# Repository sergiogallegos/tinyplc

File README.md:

# tinyplc

A research PLC built around **Structured Text → Rust frontend → LLVM IR →
ahead-of-time machine code → a C runtime on FreeRTOS/STM32**. LLVM runs on the
PC. The microcontroller schedules and executes already-compiled user logic.
The initial target is the NUCLEO-F446RE.

**Education and research only. Do not use tinyplc for real machines or safety
functions.** Output fault handling is not a certified safety system.

Repository: [sergiogallegos/tinyplc](https://github.com/sergiogallegos/tinyplc).

## Custom hardware prototype

The [hardware roadmap](docs/hardware-roadmap.md) describes a standalone tinyPLC.
The [A1 completion checklist](docs/tasks.md#a1-prototype-completion) tracks the
remaining BOM, electrical, mechanical, firmware and validation work.
The current [A1 prototype draft](hardware/prototype-a1/README.md) includes a
custom KiCad schematic and **routed two-layer PCB**, a rounded white FreeCAD
enclosure, physical power switch, OLED/status-indicator design, print files,
dimensioned drawings, BOM and official component references. Start with the
[product brochure](hardware/prototype-a1/brochure/tinyplc-a1-brochure.pdf) or the
[visual assembly guide](hardware/prototype-a1/mechanical/drawings/assembly-guide.pdf).
The PCB passes ERC and DRC with zero unrouted connections. Independent fabrication
review, physical testing, the standalone firmware port and OLED/heartbeat
integration remain outstanding. See the [routing decisions and checks](docs/hardware/prototype-a1-routing.md). The original
[A0 package](hardware/prototype-a/README.md) is preserved for comparison.

The enclosure is a Blender render; the board view comes from the routed KiCad
design. The display shows a proposed demo UI. [Rear connector view](hardware/prototype-a1/renders/rear-power.png).

## Current state: compile, download and activate native ST on STM32

Implemented: a dependency-free Rust ST frontend, positioned diagnostics,
separate typed PLC IR, textual LLVM IR emission, exported tag metadata, and a
C-compatible scan entry point. Tests verify IR, execute host machine code at
`-O0` and `-O2`, compare results with independent historical interpreters, and
cross-compile to ARM Cortex-M object code. A static FreeRTOS task now runs
linked ST machine code from RAM on the F446, samples PC13, commits PA5, latches
faults and measures the 10 ms release schedule. ST now executes in a separate
unprivileged task, with checked return, MPU isolation, TIM2 deadline abort and
IWDG reset fallback. R2 is complete; see the [consolidated report](docs/R2-report.md).

The [R3.1 wire contract](docs/wire-format.md) now defines native packages and
engineering frames, with generated Rust/C constants and golden fixtures.

[R3.2](docs/R3.2-report.md) adds the Rust native packager and portable C
package validation/staging, tested together on the host.

[R3.3](docs/R3.3-report.md) connects the board over USB serial: `plctool` downloads
into an inactive slot, explicitly activates a generation, and reports execution
status. Downloaded code runs unprivileged with validated tag bindings and a
fresh worker context. Both slots and 64-tag execution have hardware evidence.

[R3.4](docs/R3.4-report.md) adds owned snapshots and `plctool DEVICE monitor`,
with host concurrency tests and target build validation.
[R3.5](docs/R3.5-report.md) verifies the full board workflow and mixed download/monitor
traffic: a 4.054 ms maximum observed scan body within the 10 ms period, with no
missed releases in the recorded run. R3 is complete.

[R4](docs/R4.2-report.md) adds compatible VAR migration, a reserved first-scan
trial and one-use rollback to saved pre-update state. [Board evidence](docs/R4.3-report.md)
covers 64-tag reorder, contained faults, recovery failure and reset behavior.

[R5.1](docs/ton.md) adds native TON on-delay timers and millisecond TIME values,
with frozen clock input and explicit restart behavior for online changes. See
[the example](examples/ton_led.st) and [acceptance report](docs/R5.1-report.md).

**Not implemented yet:** tag writes, persistence or broader language types.

The primary compiler is `compiler/` (Rust). Earlier Python/bytecode work is
retained only as a historical semantic test reference; it is not the product
architecture or a planned fallback execution mode.

## Try it on the PC

Use existing Rust/Cargo, LLVM (`clang`, `llvm-as`, `opt`), Python 3.11+, CMake,
a C compiler, and ARM GNU ld for the package integration tests. No packages are fetched by these commands.

```sh
make compiler
./target/debug/plcc examples/button_led.st -o /tmp/button_led.ll
make run
make aot-arm
make test
```

`make run` compiles the example through Rust and LLVM, links it with a C host
harness, and prints `R1 AOT scans=5 LED=1 N=2`. `make aot-arm` creates
`build/aot/button_led.arm.o`, an ARM relocatable object. It does not upload,
link firmware, or flash a board. [Compiler usage and ABI](compiler/README.md)
and [setup](docs/setup.md) give exact reproduction commands.

## Compile, upload, and run on the board

The NUCLEO-F446RE must already have the current R5.1 runtime firmware installed
through ST-LINK. Firmware prerequisites and build instructions are in
[setup](docs/setup.md) and the [target toolchain guide](docs/target-toolchain.md).
The following workflow uploads an ST program through the ST-LINK virtual serial
port; it does not replace the runtime firmware.

After a board reset, the boot program occupies slot A and slot B is available.
Use your actual serial device path and installed toolchain paths:

```sh
make compiler
mkdir -p build/programs
PLC_DEVICE=/dev/cu.usbmodem2103
./target/debug/plctool "$PLC_DEVICE" info
./target/debug/plcpack examples/ton_led.st --slot B -o build/programs/ton-b.tplc \
  --clang /path/to/clang --ld /path/to/arm-none-eabi-ld
./target/debug/plctool "$PLC_DEVICE" download build/programs/ton-b.tplc
```

`plcpack` compiles ST, generates ARM code, links for the chosen slot, and builds
the download package. Download returns a JSON `ready_generation`; substitute
that number for `GENERATION` below:

```sh
./target/debug/plctool "$PLC_DEVICE" activate GENERATION
./target/debug/plctool "$PLC_DEVICE" status
./target/debug/plctool "$PLC_DEVICE" monitor
./target/debug/plctool "$PLC_DEVICE" update-status
```

Activation starts execution on the board's **10 ms scan cycle**. In this example,
hold BTN for 500 ms to light LED; releasing BTN clears the timer and LED on the
next invocation. `monitor` prints one coherent snapshot, including TON Q/ET
and the clock; run it again for another sample. TIME values are milliseconds.

For subsequent edits, inspect `info` and build for the inactive slot: A is
`0x20010000`, B is `0x20014000`, and ACTIVE has state 1. The download command
rejects a package built for the wrong available slot. Downloading only stages
code; `activate` is required to run it. See [package usage](packager/README.md)
and [engineering commands](engineering/README.md) for details.

Healthy online updates preserve matching scalar VAR names/types. TON instances
restart their delays. `plctool "$PLC_DEVICE" rollback` restores the saved previous
program and scalar state when a checkpoint is available; timers restart again.
Starting another download retires that checkpoint. Downloads and state are
RAM-only: reset or power loss returns to the firmware's boot program.

## How the system works

### 1. Compile on the PC; execute on the controller

```mermaid
flowchart TB
  subgraph PC["PC — frontend and AOT code generation implemented"]
    ST["ST source<br/>IEC 61131-3 subset"] --> Front["Rust frontend<br/>lexer, parser, semantic checks"]
    Front --> IR["Typed PLC IR<br/>tags, types, expressions, control flow"]
    IR --> LLVM["LLVM IR"]
    LLVM --> Object["LLVM ahead-of-time compiler<br/>ARM Cortex-M object code"]
    Object --> Experiment["Boot program<br/>static firmware link into slot A"]
    Experiment --> Runtime
    Object --> Link["Host link for slot A or B<br/>all addresses resolved on PC"]
    Link --> Package["Rust plcpack<br/>ABI, state layout, code, integrity metadata"]
  end
  Package -->|"plctool over ST-LINK USB serial"| Loader
  subgraph Board["STM32 — isolated native scan experiment implemented"]
    Loader["Low-priority C comms and loader<br/>validate, stage and seal inactive slot"]
    Loader --> Activate["Accept generation at scan boundary<br/>prepare state and protection context"]
    Activate --> Runtime["C supervisor on FreeRTOS<br/>periodically invokes native entry"]
    Runtime --> Worker["Unprivileged ST worker<br/>private stack and MPU permissions"]
    Worker --> Gate["Firmware-flash return gateway<br/>TIM2 deadline and watchdog fallback"]
    Gate --> Runtime
    Runtime --> IO["Input sampling and output commit"]
    Runtime --> Tags["Runtime-owned schema and values<br/>validated bindings, frozen I/O"]
    Tags --> Monitor["Coherent tag snapshots<br/>PC monitoring"]
  end
  classDef implemented fill:#e1f5ef,stroke:#39927d,color:#064f43;
  classDef planned fill:#f2f2f2,stroke:#888,color:#333;
  class ST,Front,IR,LLVM,Object,Link,Package,Experiment,Runtime,Worker,Gate,IO,Loader,Activate,Tags implemented;
  class Monitor implemented;
```

Green is implemented; the R3.4 report distinguishes host tests from board evidence. The C
runtime is firmware installed through ST-LINK. The user program is a separate
native artifact downloaded through the engineering connection. A general
Linux `.so` or an unqualified raw `.bin` is not our MCU loading contract.

### 2. Scan ownership and monitoring

**Full target design.** Scheduling, sampled inputs, working/committed state,
physical outputs, fault latching, unprivileged execution and native deadline
abort are implemented in the [scan supervisor](docs/scan-runtime.md) and
[execution boundary](docs/native-isolation.md). Owned tag snapshots are implemented in R3.4; tag-write boundary requests remain planned.

```mermaid
flowchart TB
  subgraph Scan["C scan supervisor — highest application priority"]
    Read["Sample physical inputs<br/>freeze input image"] --> Working["Prepare working state<br/>arm deadline guard"]
    Working --> Run["Invoke compiled native logic<br/>bounded unprivileged execution"]
    Run --> Check["Trusted return or abort<br/>commit success / discard failed work"]
    Check --> Outputs["Apply physical outputs<br/>FALSE on fault"]
    Outputs --> Publish["Publish coherent snapshot<br/>tags, scan ID, generation, diagnostics"]
    Publish --> Boundary["Apply accepted boundary request<br/>then wait for next release"]
    Boundary --> Read
  end
  subgraph Comms["Lower-priority engineering task"]
    Receive["Receive command"] --> Stage["Stage native image<br/>validate before READY"]
    Receive --> Request["Request activation/rollback<br/>bounded payload + generation"]
    Receive --> Monitor["Read owned snapshot<br/>respond to PC monitor"]
  end
  Request -. "scan owner applies" .-> Boundary
  Publish -. "three-buffer ownership mailbox" .-> Monitor
  Working -. "independent guard interrupts a stuck program" .-> Abort["Abort user context<br/>output policy + fault recovery"]
```

Comms never reads a tag by racing a live write or retaining a pointer into a
reusable program slot. A snapshot contains values **and** names/types/scan and
generation identifiers. A slow monitor may miss scans without blocking the
producer. Tag writes remain unimplemented; the planned design routes them through the scan owner.

Native code addresses fields relative to a supplied state block. The symbol
metadata maps names to types/classes and offsets; it does not embed arbitrary
addresses in privileged runtime memory. Inputs are frozen and outputs are
proposals until commit. The initial research ABI uses one u32 cell per tag,
with byte offset `4 × declaration index`.

### 3. Edit, download, accept, observe

**Implemented download/activation workflow.** Download success and activation
success are separate states; R3.4 adds coherent tag snapshots.

```mermaid
sequenceDiagram
  actor User as Engineer
  participant PC as Rust frontend + LLVM + engineering CLI
  participant Loader as C loader / comms
  participant Scan as FreeRTOS scan supervisor
  User->>PC: Edit ST and build target native image
  PC->>Loader: Transfer bounded chunks
  Loader->>Loader: Validate package, ABI, exact slot and state schema
  Loader-->>PC: READY with candidate generation
  Note over Loader,Scan: Current program keeps running
  User->>PC: Accept edit
  PC->>Loader: ACTIVATE(candidate generation)
  Loader-->>PC: Request accepted, not yet running
  Loader->>Scan: Publish owned boundary request
  Scan->>Scan: Migrate compatible VARs and install a fresh native worker
  Scan->>Scan: Execute first candidate scan under deadline guard
  alt Successful execution
    Scan-->>Loader: Snapshot confirms running generation
  else Contained application fault
    Scan->>Scan: Outputs FALSE, discard candidate working state
    Scan->>Scan: Restore healthy checkpoint at the next release, if available
    Scan-->>Loader: Fault and rejected generation retained
  end
  PC->>Loader: Read execution status
  Loader-->>PC: Actual generation, outcome, fault and timing
  PC-->>User: Confirm the edit outcome
```

R4 migration matches exact internal variable names and types. Explicit rollback
restores saved pre-update values and consumes its checkpoint.
Inputs are resampled and outputs recomputed. Preserved variables do not
promise unchanged output behavior; rollback cannot undo physical actions.
Two slots cannot preserve active, previous, and another candidate at once.
Slot reservations and generation checks are required; a pending flag and
pointer flip alone are insufficient.

## Structured Text scope

The initial language is a small **IEC 61131-3-inspired ST subset**, not full
IEC conformance: BOOL, DINT, TIME, input/output/internal declarations,
assignments, IF/ELSIF/ELSE, DINT arithmetic, comparisons, eager boolean logic,
comments, and TON on-delay timers with IN/PT inputs and Q/ET outputs.
TIME supports nonnegative millisecond durations and comparisons, not arithmetic.
See [language.md](docs/language.md) and [TON](docs/ton.md) for exact grammar,
clock behavior, and limits: 64 expanded cells, including five per timer and one
shared clock cell. General function blocks and loops are not supported.

```iecst
PROGRAM Main
VAR_INPUT BTN : BOOL; END_VAR
VAR_OUTPUT LED : BOOL; END_VAR
VAR n : DINT; END_VAR
IF BTN THEN n := n + 1; END_IF;
LED := NOT BTN;
END_PROGRAM
```

`N` increments on every scan with BTN pressed, not once per press. DINT wraps
modulo 2^32. Division by zero reports a fault; minimum DINT divided by -1 wraps.
The Rust emitter preserves these rules explicitly instead of relying on LLVM
undefined behavior. [LLVM division semantics](https://llvm.org/docs/LangRef.html#sdiv-instruction).

## Hardware

The NUCLEO-F446RE contains an STM32F446RE Cortex-M4F, an onboard ST-LINK/V2-1 debugger, a user LED, and a user button. Connect a USB **data** cable to ST-LINK CN1. No external I/O circuitry is needed for the first example. This board provides 3.3 V logic; industrial 24 V inputs and outputs would need separate conditioning and protection hardware.

| Resource | Project mapping | Verification and qualification |
| --- | --- | --- |
| LD2 green user LED | `LED` → PA5, HIGH lights it | UM1724 §7.6 and Table 19 |
| B1 user button | `BTN` → PC13, inverted for pressed = TRUE | UM1724 §7.7 confirms pin; polarity must match board schematic/revision before hardware acceptance |
| ST-LINK virtual COM port | USART2: PA2 TX, PA3 RX | UM1724 §7.10, default solder bridges SB13/SB14 connected |
| Serial configuration | 115200 baud, 8 data bits, no parity, 1 stop bit | Chosen firmware setting, not a fixed hardware setting |
| Memory | 512 KB flash, 128 KB main SRAM | STM32F446xC/E datasheet; also 4 KB backup SRAM, unused in v1 |
| Ethernet | No onboard Ethernet interface | Use UART on the board; host TCP transport is planned |

On macOS a VCP commonly appears as `/dev/tty.usbmodem*` and `/dev/cu.usbmodem*`; discover the actual path rather than hardcoding it. A detected device does not prove the firmware works. The hardware references are [ST UM1724 Rev 17](https://www.st.com/resource/en/user_manual/dm00105823.pdf), [STM32F446 datasheet](https://www.st.com/resource/en/datasheet/stm32f446re.pdf), and [MB1136 C04 schematic, MCU sheet](https://www.st.com.cn/resource/en/schematic_pack/mb1136-default-c04_schematic.pdf). The requested facts are consistent with these qualifications: baud and Mac device path are configuration/environment choices, and 128 KB excludes backup SRAM.

The Rust CLI currently uses built-in logical bindings for `BTN` (BOOL input)
and `LED` (BOOL output). The [board profile](boards/nucleo_f446re.json) records
the physical mapping; the C board port applies it. The compiler library
also accepts an explicit list of logical bindings. No register access is emitted
into user logic.

See the [educational design and compiler/runtime studies](docs/education.md) for the reading
order, dependency boundary, and reasons for using a small STM32 board.

## Repository responsibilities

| Directory | Role |
| --- | --- |
| `compiler/` | Primary Rust lexer/parser, semantic analysis, typed PLC IR, LLVM emitter, CLI, scan ABI, tests |
| `contract/` | Shared wire definitions and generated Rust/C constants |
| `packager/`, `engineering/` | Rust native package builder and serial engineering CLI |
| `runtime/` | Portable C scan transaction, package validator, staging and framing |
| `sim/aot_main.c` | Current C harness invoking host AOT machine code |
| `port/` | STM32 C/FreeRTOS supervisor, GPIO/UART, MPU, deadline and fault handling; historical blink |
| `tests/llvm/` | IR verification, optimized host AOT execution, ARM codegen and semantic comparisons |
| `boards/` | Explicit target I/O mapping; native profiles are documented in `docs/` |
| `core/`, `host/`, `tests/native/` | Historical M1/M2 implementation and independent test oracles |
| `docs/` | Current architecture, compiler contract, native loader roadmap, reports and historical designs |

The Rust frontend uses only its standard library. LLVM is a PC-side toolchain
dependency; no LLVM library or compiler runs on the MCU. FreeRTOS is the
scheduler dependency. The project owns PLC semantics, the native image/ABI
contract, engineering operations, and runtime state management.

## Roadmap after the architecture change

| Stage | Deliverable | Status |
| --- | --- | --- |
| M0–M2 | Initial board scaffold, C VM, Python compiler and independent execution tests | Historical; retained for evidence and test reuse |
| R1 | Rust ST frontend → typed PLC IR → LLVM IR; host AOT and Cortex-M object generation | Implemented and host-tested |
| R2 | Native ABI/package contract, C supervisor, bounded static native execution and fault containment on F446 | Complete, including hardware evidence |
| R3 | Native loader, upload protocol, engineering CLI and coherent tag monitoring | Complete, including board monitoring and mixed-traffic timing |
| R4 | Online state migration, first-scan trial and explicit/automatic rollback | Implemented and verified on the board |
| R5.1 | TON on-delay timers, TIME, frozen clock input and restart-on-update behavior | Complete, including host and board acceptance |
| Further R5 work | Additional language features, source debugging, persistence and target ports | Future extensions |

R1 replaces the earlier bytecode-first roadmap. No MCU loading, RTOS timing,
or hardware acceptance is implied by host tests. [Runtime architecture](docs/architecture.md)
explains ownership and recovery; [native roadmap](docs/native-roadmap.md)
compares the learning project with a production prototype and specifies target
acceptance gates. [M1](docs/M1-report.md) and [M2](docs/M2-report.md) remain dated
records, not current implementation instructions. Project code is MIT licensed.

## Acknowledgments and next tasks

The educational approach is inspired by Andrej Karpathy's micrograd and nanoGPT.
We study Rusty, OpenPLC Runtime and matiec for compiler/runtime design lessons.
tinyplc remains an independent implementation with its own small scope and
contracts. See [references and acknowledgments](docs/references.md) for credits,
official Rust/C/LLVM/FreeRTOS/STM32 documentation, and the attribution policy.

The [task checklist](docs/tasks.md) records completed work, acceptance evidence
and open decisions. R1 and the R2.1 [target call ABI draft](docs/native-abi.md) are complete.
The compiler supports `--abi 2`; the ST example now runs from RAM in a
FreeRTOS board experiment with an unprivileged native worker. R2.2 [toolchain and MPU-port selection](docs/target-toolchain.md) is
recorded; [R2.3](docs/R2.3-report.md) and [R2.4](docs/R2.4-report.md) now include hardware evidence.

R2.3 now has a [buildable FreeRTOS layout scaffold](docs/memory-layout.md)
and checked ELF memory boundaries. Its privileged supervisor schedules LLVM-generated
ST with physical input/output supervision; [R2.5](docs/R2.5-report.md) records
GPIO, fault-latch and scan-timing evidence. [R2.6](docs/R2.6-report.md) adds
unprivileged protection, checked return/abort and watchdog recovery. Package
requirements and fixed-slot placement are defined in [R2.7](docs/native-package.md).
The [R2 report](docs/R2-report.md) closes this stage. [R3.1](docs/R3.1-report.md) freezes shared package/protocol encoding and golden
fixtures. [R3.2](docs/R3.2-report.md) adds the Rust packager and bounded C
validation/staging. [R3.3](docs/R3.3-report.md) implements USB serial download
and board activation. [R3.4](docs/R3.4-report.md) implements coherent tag snapshots
and PC monitoring. [R3.5](docs/R3.5-report.md) closes the board workflow and timing
gate. [R4.1](docs/online-state.md) defines migration, initialization and rollback
state semantics. [R4.2](docs/R4.2-report.md) implements them and
[R4.3](docs/R4.3-report.md) records board acceptance. [R5.1](docs/R5.1-report.md)
adds verified TON/TIME support. Further extensions remain future work, selected
from a documented need.

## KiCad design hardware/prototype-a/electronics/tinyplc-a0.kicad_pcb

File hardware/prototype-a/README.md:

# tinyPLC A0 prototype

Started 2026-10-24 at the user's request. This is an editable standalone STM32
engineering prototype draft, with a matching printable enclosure and assembly
documentation. A0 is a starting revision for review and iteration.

**The PCB is placed and electrically connected in the design database, but is
unrouted. It cannot be fabricated as a working controller yet.** No Gerbers or
order package are supplied. The BOM contains candidate parts and explicitly
unselected capacitor SKUs; it is not an approved purchasing list. The case can
be printed for a fit experiment now. No physical assembly has been tested.

## Open and inspect

| File | Purpose |
| --- | --- |
| [KiCad project](electronics/tinyplc-a0.kicad_pro) | Open in KiCad 10; schematic and placed PCB share pin-level nets |
| [Schematic PDF](electronics/tinyplc-a0-schematic.pdf) | Printable circuit atlas; equal net labels connect electrically |
| [PCB placement drawing](electronics/tinyplc-a0-placement.svg) | Actual KiCad footprint placement; no routed copper yet |
| [FreeCAD assembly](mechanical/tinyplc-a0.FCStd) | Editable spreadsheet, primitive and Boolean feature trees, board and package envelopes |
| [Assembly STEP](mechanical/tinyplc-a0-assembly.step) | Neutral-format enclosure, board and approximate packages |
| [Blender scene](renders/tinyplc-a0.blend) | Native assembled scene; render script also creates an exploded view |
| [Assembled preview](renders/tinyplc-a0-assembled.png) | CAD-based appearance preview |
| [Exploded preview](renders/tinyplc-a0-exploded.png) | Case, board and lid relationship |
| [Electronic BOM](bom/electronics.csv) | Reference, quantity, candidate MPN, purpose, official documentation and status |
| [Mechanical BOM](bom/mechanical.csv) | Printed parts, fasteners, wiring and external equipment |
| [Drawing package](mechanical/drawings/README.md) | Dimensioned A4 PDF/SVG drawings and a PCB fit template |
| [Combined drawing PDF](mechanical/drawings/tinyplc-a0-drawings.pdf) | Four sheets, retaining true-size A4 dimensions |
| [Visual assembly booklet](mechanical/drawings/assembly-guide.pdf) | Color CAD renders, parts inventory, assembly arrows and one action per step |
| [Technical assembly reference](mechanical/drawings/technical-assembly-reference.pdf) | Detailed printing, staged electronic assembly and electrical bring-up instructions |
| [Illustration scene](renders/assembly/assembly-illustrations.blend) | Editable Blender assembly illustrations, including nominal fasteners |
| [Assembly guide](../../docs/hardware/prototype-a-assembly.md) | Step-by-step print, assembly and bring-up sequence |

Start reading with the [electrical explanation](../../docs/hardware/prototype-a-electronics.md),
[component-by-component register](../../docs/hardware/prototype-a-components.md),
and [mechanical decisions](../../docs/hardware/prototype-a-mechanics.md).

## Agreed direction and explicit assumptions

The user authorized creating an initial PCB and case, using KiCad/FreeCAD, with
an optional Blender render; documenting decisions, every component and official
references; and supplying printable drawings and a step-by-step assembly guide.
No purchases or manufacturing orders were authorized or made.

The standalone board option was used to start work, following the existing
hardware roadmap. No user reply choosing a Nucleo carrier has been received.
Budget, printer, soldering equipment and final electrical ratings remain open.
All dimensions and component selections below are revisable assumptions.

- STM32F446RET6 in LQFP64; 120 × 90 × 1.6 mm PCB.
- Clean regulated 24 V bench supply, initially 21.6–26.4 V only.
- Four active-low input stages with optocouplers, sharing ground with the MCU.
- Four sinking outputs; initial test target 50 mA per channel, 200 mA total,
  resistive loads only. These are test targets, not verified ratings.
- On-board 3.3 V converter. No USB-to-board power path.
- Native USB-C circuitry reserved for new USB device firmware. The existing
  serial engineering protocol will first use a separate 3.3 V UART adapter.
- Optional display and Ethernet use cabled expansion headers. There is no
  selected direct-plug Ethernet footprint, RJ45 aperture, or display mounting
  adapter. Rendered lid opening has a real removable blank, not a fake screen.
- Case 132 × 102 × 32.4 mm, plus 2 mm display blank; screwed lid, no DIN clip.

## Revision and verification

[verification.md](reports/verification.md) records tool versions and measured CAD
checks. ERC is an electrical connectivity/rules check; it cannot establish
correct resistor calculations, circuit performance, fabrication readiness or
firmware operation. DRC reports preserve the unrouted connections.

The next electrical revision must finish BOM selection, review the schematic
and footprints, complete routing, select fabrication constraints and verify
clearances/current paths. Prototype the I/O stages on the Nucleo in parallel.
Then generate a separate manufacturing release with measured bring-up results.

## Regeneration and editing

Generated CAD can be edited directly in its native application. **Regeneration
replaces CAD and BOM outputs. Save manual changes under a new revision before
running generators.** There is no automatic bidirectional synchronization from
native CAD back to Python/JSON.

```sh
python3 hardware/prototype-a/scripts/generate_electronics.py
python3 hardware/prototype-a/scripts/generate_mechanics.py
python3 hardware/prototype-a/scripts/generate_drawings.py
blender --background --threads 6 --python hardware/prototype-a/scripts/render_blender.py
blender --background --threads 6 --python hardware/prototype-a/scripts/render_assembly.py
python3 hardware/prototype-a/scripts/generate_assembly_guide.py
python3 hardware/prototype-a/scripts/verify.py
```

The installed system Python provides KiCad's `pcbnew`; FreeCAD libraries are
loaded from `/usr/lib/freecad/lib`. No dependency downloads are performed.
The drawing script invokes `rsvg-convert` and `pdfunite` for PDF export. Changing layout needs
coordinated updates to the PCB generator, case openings and drawing generator;
`parameters.json` records the overall envelope, not a universal enclosure solver.

The visual booklet is generated separately from the technical text reference.
Its editable, self-contained SVG pages and individual PDFs are in
`mechanical/drawings/assembly-pages/`; source renders and camera-projected arrow
coordinates are in `renders/assembly/`. The illustrations use actual exported
case/board meshes, simplified package envelopes and nominal hardware. Colors
identify parts; they do not specify filament or hardware finishes. The case
geometry is unchanged. Lid text shown in renders represents separately applied
labels, not embossed print geometry.

Third-party KiCad library assets retain their [library license](electronics/THIRD_PARTY.md).
Original prototype scripts and documentation follow the repository license.
Hardware licensing for a future published manufacturing release remains open.

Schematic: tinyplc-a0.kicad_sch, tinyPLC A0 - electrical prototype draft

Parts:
C1: 22uF / 50V; CP_Radial_D6.3mm_P2.50mm; MPN Panasonic EEU-FR1H220
C2, C4, C5, C6, C7, C10, C12, C30, C31: 100nF / 50V; C_0805_2012Metric; MPN TDK C2012 family; exact MPN pending
C3: 10uF / 10V; C_0805_2012Metric; MPN TDK C2012 family; exact MPN pending
C8, C9: 4.7uF / 10V; C_0805_2012Metric; MPN TDK C2012 family; exact MPN pending
C11: 1uF / 10V; C_0805_2012Metric; MPN TDK C2012 family; exact MPN pending
C13, C14: 27pF C0G / 50V; C_0805_2012Metric; MPN TDK C2012 family; exact MPN pending
C21, C22, C23, C24: 10nF / 50V; C_0805_2012Metric; MPN TDK C2012 family; exact MPN pending
D1: SS16; D_SMA; MPN SS16
D2: GREEN; LED_0805_2012Metric; MPN Kingbright KP-2012SGC
D11, D12, D13, D14: 1N4148W; D_SOD-123; MPN 1N4148W
F1: 500mA / 60V; PTC_MF_R050; MPN MF-R050
H1, H2, H3, H4: M3 NPTH; MountingHole_3.2mm_M3; MPN No purchased component
J1: 24V IN / GND; TerminalBlock_Phoenix_MKDS-1,5-2-5.08_1x02_P5.08mm_Horizont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; MPN 1715721
J2: BOOT: 1=3V3 2=BOOT0 3=GND; PinHeader_1x03_P2.54mm_Vertical; MPN Samtec TSW-103-07-G-S
J3: SWD: 3V3 GND DIO CLK NRST SWO; PinHeader_1x06_P2.54mm_Vertical; MPN Samtec TSW-106-07-G-S
J4: UART: GND TX RX; PinHeader_1x03_P2.54mm_Vertical; MPN Samtec TSW-103-07-G-S
J5: DI1 / GND; TerminalBlock_Phoenix_MKDS-1,5-2-5.08_1x02_P5.08mm_Horizont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; MPN 1715721
J6: DI2 / GND; TerminalBlock_Phoenix_MKDS-1,5-2-5.08_1x02_P5.08mm_Horizont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; MPN 1715721
J7: DI3 / GND; TerminalBlock_Phoenix_MKDS-1,5-2-5.08_1x02_P5.08mm_Horizont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; MPN 1715721
J8: DI4 / GND; TerminalBlock_Phoenix_MKDS-1,5-2-5.08_1x02_P5.08mm_Horizont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; MPN 1715721
J9: +24 / Q1 sink; TerminalBlock_Phoenix_MKDS-1,5-2-5.08_1x02_P5.08mm_Horizont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; MPN 1715721
J10: +24 / Q2 sink; TerminalBlock_Phoenix_MKDS-1,5-2-5.08_1x02_P5.08mm_Horizont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; MPN 1715721
J11: +24 / Q3 sink; TerminalBlock_Phoenix_MKDS-1,5-2-5.08_1x02_P5.08mm_Horizont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; MPN 1715721
J12: +24 / Q4 sink; TerminalBlock_Phoenix_MKDS-1,5-2-5.08_1x02_P5.08mm_Horizont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; MPN 1715721
J13: USB-C DEVICE; USB_C_Receptacle_GCT_USB4105-xx-A_16P_TopMnt_Horizontal; MPN USB4105-GF-A-120
J14: SPI: 3V3 GND SCK MISO MOSI CS; PinHeader_1x06_P2.54mm_Vertical; MPN Samtec TSW-106-07-G-S
J15: ETH: GND RST INT; PinHeader_1x03_P2.54mm_Vertical; MPN Samtec TSW-103-07-G-S
J16: OLED: 3V3 GND SCL SDA; PinHeader_1x04_P2.54mm_Vertical; MPN Samtec TSW-104-07-G-S
R1, R62, R63: 22; R_0805_2012Metric; MPN ERJ-6ENF22R0V
R2, R3, R4, R5, R12, R22, R32, R42, R70, R71, R72: 10k; R_0805_2012Metric; MPN ERJ-6ENF1002V
R6: 1k; R_0805_2012Metric; MPN ERJ-6ENF1001V
R10, R11, R20, R21, R30, R31, R40, R41: 2.2k; R_0805_2012Metric; MPN ERJ-6ENF2201V
R51, R52, R53, R54, R65: 100k; R_0805_2012Metric; MPN ERJ-6ENF1003V
R60, R61: 5.1k; R_0805_2012Metric; MPN ERJ-6ENF5101V
R64: 68k; R_0805_2012Metric; MPN ERJ-6ENF6802V
R73, R74: 4.7k; R_0805_2012Metric; MPN ERJ-6ENF4701V
SW1: RESET; SW_PUSH_6mm; MPN Omron B3F-1000
SW2: USER; SW_PUSH_6mm; MPN Omron B3F-1000
TP1: GND; TestPoint_Pad_D2.0mm; MPN Bare PCB test pad
TP2: +3V3; TestPoint_Pad_D2.0mm; MPN Bare PCB test pad
TP3: V24; TestPoint_Pad_D2.0mm; MPN Bare PCB test pad
TP4: VCAP1; TestPoint_Pad_D2.0mm; MPN Bare PCB test pad
U1: STM32F446RET6; LQFP-64_10x10mm_P0.5mm; MPN STM32F446RET6
U2: TSR 1-2433; Converter_DCDC_TRACO_TSR-1_THT; MPN TSR 1-2433
U3: TPL7407LDR; SOIC-16_3.9x9.9mm_P1.27mm; MPN TPL7407LDR
U4, U5, U6, U7: VO617A-3; DIP-4_W7.62mm; MPN VO617A-3
U8: USBLC6-2SC6; SOT-23-6; MPN USBLC6-2SC6
Y1: 8MHz CL18pF; Crystal_SMD_5032-2Pin_5.0x3.2mm; MPN ABM3-8.000MHZ-B2-T

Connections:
/+3V3: C3.1, C4.1, C5.1, C6.1, C7.1, C9.1, J2.1, J3.1, J14.1, J16.1, R1.1, R2.2, R5.2, R12.1, R22.1, R32.1, R42.1, R70.2, R72.2, R73.2, R74.2, TP2.1, U1.1 (VBAT), U1.19 (VDD), U1.32 (VDD), U1.48 (VDD), U1.64 (VDD), U2.3 (3V3)
/BOOT0: J2.2, R3.1, U1.60 (BOOT0)
/BOOT1: R4.1, U1.28 (PB2)
/BTN_N: R5.1, SW2.1, U1.2 (PC13)
/CC1: J13.A5 (CC1), R60.1
/CC2: J13.B5 (CC2), R61.1
/DI1_24: J5.1, R10.1
/DI1_A: D11.1 (K), R11.2, U4.1
/DI1_MID: R10.2, R11.1
/DI1_N: C21.1, R12.2, U1.14 (PA0), U4.4
/DI2_24: J6.1, R20.1
/DI2_A: D12.1 (K), R21.2, U5.1
/DI2_MID: R20.2, R21.1
/DI2_N: C22.1, R22.2, U1.15 (PA1), U5.4
/DI3_24: J7.1, R30.1
/DI3_A: D13.1 (K), R31.2, U6.1
/DI3_MID: R30.2, R31.1
/DI3_N: C23.1, R32.2, U1.20 (PA4), U6.4
/DI4_24: J8.1, R40.1
/DI4_A: D14.1 (K), R41.2, U7.1
/DI4_MID: R40.2, R41.1
/DI4_N: C24.1, R42.2, U1.22 (PA6), U7.4
/DO1: R51.1, U1.26 (PB0), U3.1 (IN1)
/DO2: R52.1, U1.27 (PB1), U3.2 (IN2)
/DO3: R53.1, U1.61 (PB8), U3.3 (IN3)
/DO4: R54.1, U1.62 (PB9), U3.4 (IN4)
/ETH_CS_N: J14.6, R70.1, U1.33 (PB12)
/ETH_INT_N: J15.3, R72.1, U1.41 (PA8)
/ETH_RST_N: J15.2, R71.1, U1.43 (PA10)
/GND: C1.2, C2.2, C3.2, C4.2, C5.2, C6.2, C7.2, C8.2, C9.2, C10.2, C11.2, C12.2, C13.2, C14.2, C21.2, C22.2, C23.2, C24.2, C30.2, C31.2, D2.1 (K), D11.2 (A), D12.2 (A), D13.2 (A), D14.2 (A), J1.2, J2.3, J3.2, J4.1, J5.2, J6.2, J7.2, J8.2, J13.A1 (GND), J13.A12 (GND), J13.B1 (GND), J13.B12 (GND), J13.SH (SHIELD), J14.2, J15.1, J16.2, R3.2, R4.2, R51.2, R52.2, R53.2, R54.2, R60.2, R61.2, R65.2, R71.2, SW1.2, SW2.2, TP1.1, U1.12 (VSSA), U1.18 (VSS), U1.31 (VSS), U1.47 (VSS), U1.63 (VSS), U2.2 (GND), U3.5 (IN5), U3.6 (IN6), U3.7 (IN7), U3.8 (GND), U4.2, U4.3, U5.2, U5.3, U6.2, U6.3, U7.2, U7.3, U8.2 (GND)
/I2C_SCL: J16.3, R73.1, U1.58 (PB6)
/I2C_SDA: J16.4, R74.1, U1.59 (PB7)
/LED_A: D2.2 (A), R6.2
/NRST: C12.1, J3.5, R2.1, SW1.1, U1.7 (NRST)
/OSC_IN: C13.1, U1.5 (PH0), Y1.1
/OSC_OUT: C14.1, U1.6 (PH1), Y1.2
/Q1: J9.2, U3.16 (OUT1)
/Q2: J10.2, U3.15 (OUT2)
/Q3: J11.2, U3.14 (OUT3)
/Q4: J12.2, U3.13 (OUT4)
/SPI2_MISO: J14.4, U1.35 (PB14)
/SPI2_MOSI: J14.5, U1.36 (PB15)
/SPI2_SCK: J14.3, U1.34 (PB13)
/STATUS_LED: R6.1, U1.21 (PA5)
/SWCLK: J3.4, U1.49 (PA14)
/SWDIO: J3.3, U1.46 (PA13)
/UART_RX: J4.3, U1.17 (PA3)
/UART_TX: J4.2, U1.16 (PA2)
/USB_DM: R62.2, U1.44 (PA11)
/USB_DM_CONN: J13.A7 (D-), J13.B7 (D-), R62.1, U8.1 (I/O1), U8.6 (I/O1)
/USB_DP: R63.2, U1.45 (PA12)
/USB_DP_CONN: J13.A6 (D+), J13.B6 (D+), R63.1, U8.3 (I/O2), U8.4 (I/O2)
/USB_VBUS_SENSE: R64.2, R65.1, U1.42 (PA9)
/V24: C1.1, C2.1, C30.1, D1.1 (K), J9.1, J10.1, J11.1, J12.1, TP3.1, U2.1 (VIN), U3.9 (COM)
/VBUS_USB: C31.1, J13.A4 (VBUS), J13.A9 (VBUS), J13.B4 (VBUS), J13.B9 (VBUS), R64.1, U8.5 (VBUS)
/VCAP1: C8.1, TP4.1, U1.30 (VCAP_1)
/VDDA: C10.1, C11.1, R1.2, U1.13 (VDDA)
/VIN24: F1.1, J1.1
/VIN_FUSED: D1.2 (A), F1.2

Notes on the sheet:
A0 ENGINEERING DRAFT - net labels connect equal names; NC crosses mark intentionally unused pins
Native USB / Ethernet / OLED need new firmware. PCB is deliberately unrouted. No verified electrical ratings yet.
POWER
MCU
INPUT 1
INPUT 2
INPUT 3
INPUT 4
OUTPUTS
USB
EXPANSION
TEST POINTS
MOUNTING

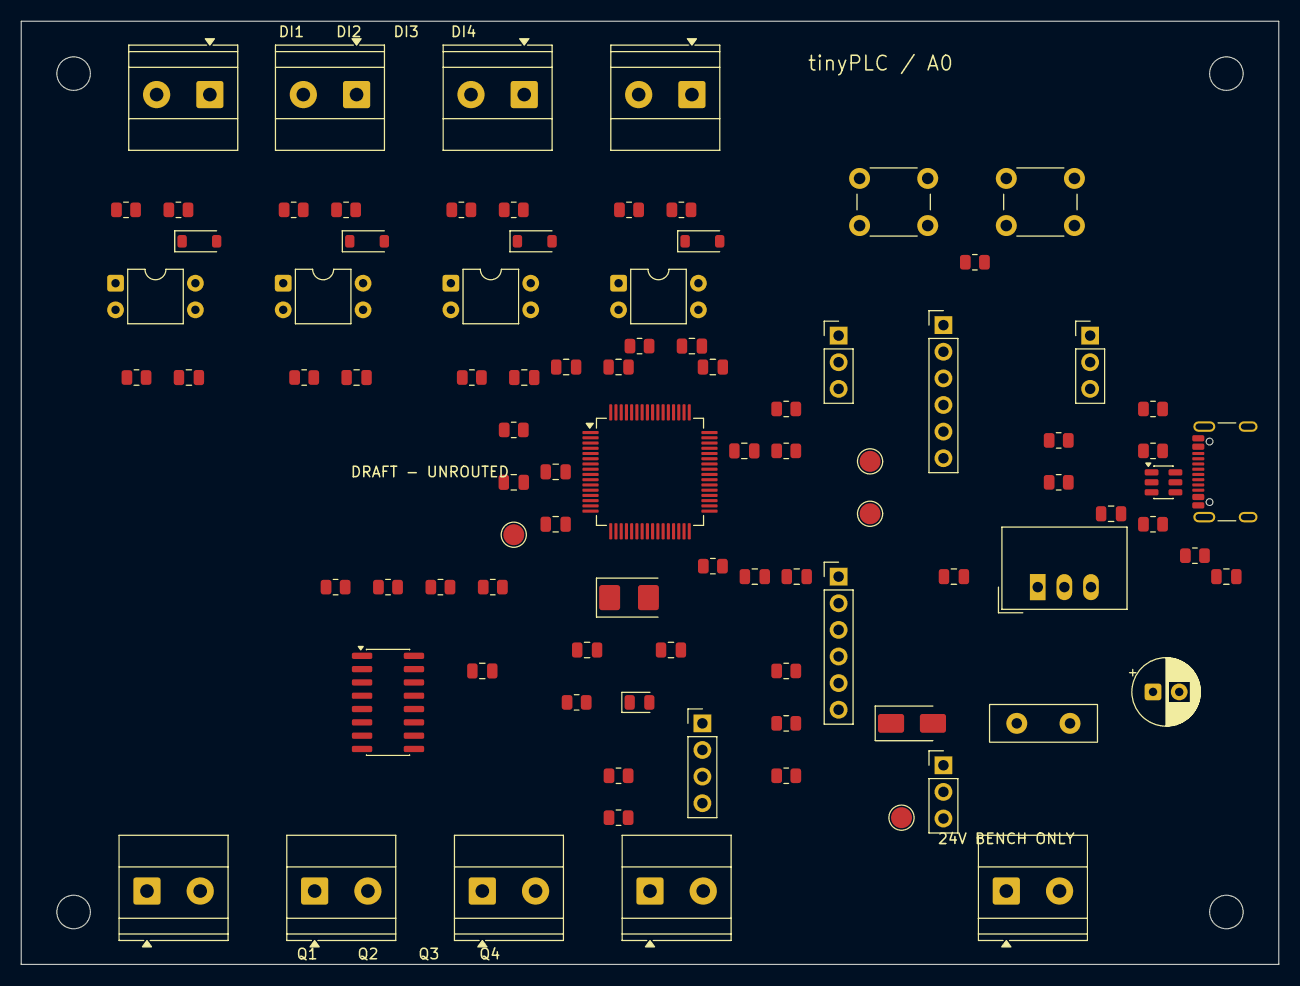
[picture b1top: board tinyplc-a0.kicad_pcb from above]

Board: 2 copper layers, 120.0 x 90.0 mm, 95 parts (0 on the bottom side), 59 nets, no tracks yet.
